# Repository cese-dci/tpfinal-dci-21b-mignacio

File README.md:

## Trabajo práctico final de la asignatura DCI ##
Este repositorio contiene el trabajo práctico final para la asignatura de Diseño de Circuitos Impresos de la carrera de posgrado de FIUBA.

* Autor: Ignacio Moya
* Título corto del trabajo:  Poncho MAX9924 para EDU-CIAA 
* Descripción:  Poncho para el circuito integrado MAX9924, que funciona como interface para sensores de reluctancia variable.

## Licencia de este trabajo ##
GPL http://www.gnu.org/licenses/gpl-3.0.html

## Estructura del repositorio ##

* doc: Toda la información sobre el circuito, principalmente de autoría o procesamiento propio. Por ejemplo:
  * Notas de ingeniería propias.
  * Notas de aplicación propias.
  * Estudios previos, estado del arte, resumen de las investigaciones.
  * Notas con cálculos.
  * Dibujos adicionales.
  * Fotos de los prototipos.
  * Presupuestos, cotizaciones.
* info: Toda la iformación recolectada, principalmente de terceros, como por ejemplo:
  * Hojas de datos.
  * Notas de aplicación.
  * Info de productos comerciales.
  * Info en internet.
* pcb: Archivos de diseño esquemático y pcb.

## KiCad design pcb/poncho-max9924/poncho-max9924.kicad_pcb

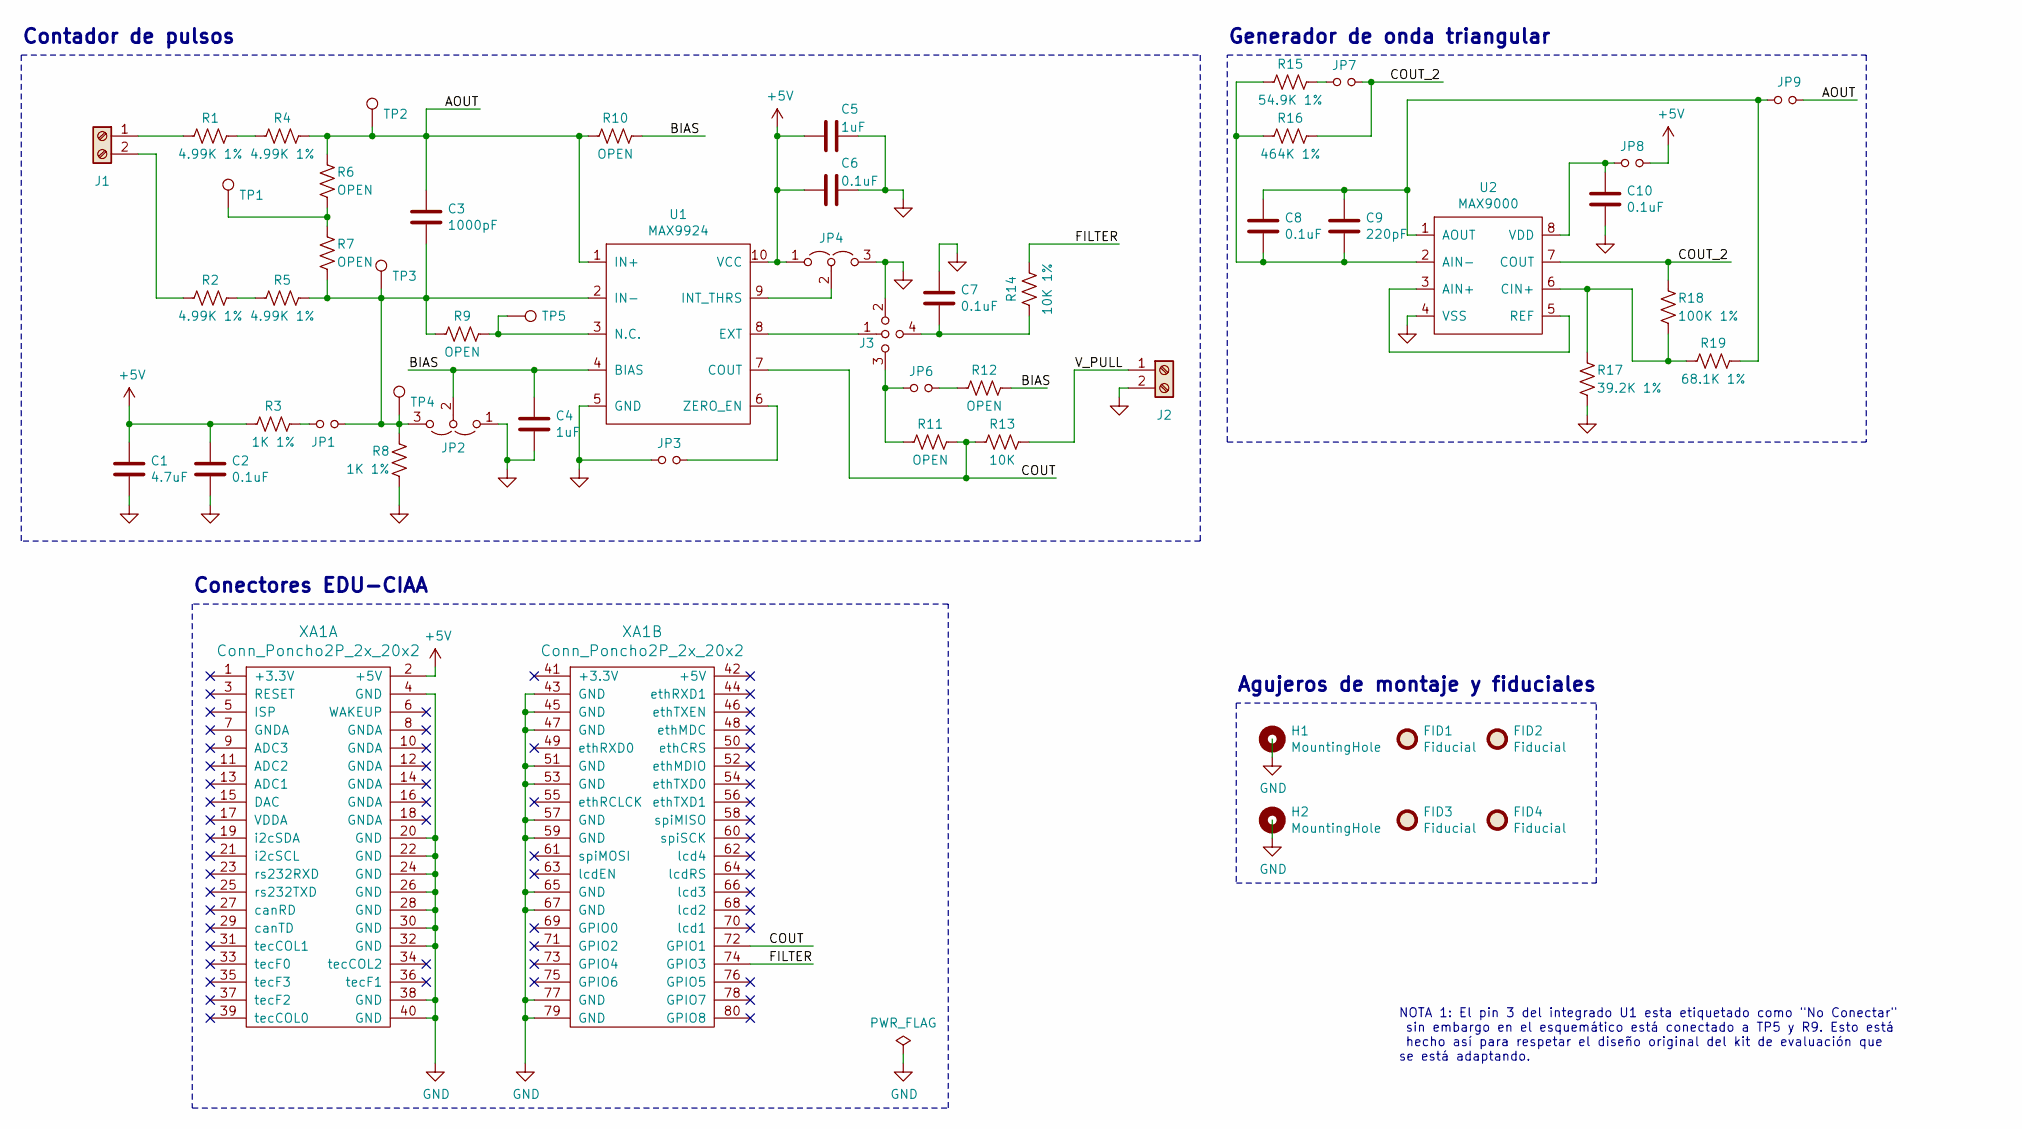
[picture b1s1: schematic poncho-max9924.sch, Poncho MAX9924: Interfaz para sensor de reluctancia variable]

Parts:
C1: 4.7uF; C_0805_2012Metric_Pad1.18x1.45mm_HandSolder
C2, C6, C7, C8, C10: 0.1uF; C_0805_2012Metric_Pad1.18x1.45mm_HandSolder
C3: 1000pF; C_0805_2012Metric_Pad1.18x1.45mm_HandSolder
C4, C5: 1uF; C_0805_2012Metric_Pad1.18x1.45mm_HandSolder
C9: 220pF; C_0805_2012Metric_Pad1.18x1.45mm_HandSolder
FID1, FID2, FID3, FID4: Fiducial; Fiducial_0.5mm_Mask1mm
H1, H2: MountingHole; MountingHole_3.5mm_Pad
J1, J2: Screw_Terminal_01x02; TerminalBlock_bornier-2_P5.08mm
J3: jumper_4_open; PinHeader_1x03_1x01_P2.54mm_Vertical
JP1, JP3, JP6, JP7, JP8, JP9: Jumper_NO_Small; PinHeader_1x02_P2.54mm_Vertical
JP2, JP4: Jumper_3_Open; PinHeader_1x03_P2.54mm_Vertical
R1, R2, R4, R5: 4.99K 1%; R_0805_2012Metric_Pad1.20x1.40mm_HandSolder
R3, R8: 1K 1%; R_0805_2012Metric_Pad1.20x1.40mm_HandSolder
R6, R7, R9, R10, R11, R12: OPEN; R_0805_2012Metric_Pad1.20x1.40mm_HandSolder
R13: 10K; R_0805_2012Metric_Pad1.20x1.40mm_HandSolder
R14: 10K 1%; R_0805_2012Metric_Pad1.20x1.40mm_HandSolder
R15: 54.9K 1%; R_0805_2012Metric_Pad1.20x1.40mm_HandSolder
R16: 464K 1%; R_0805_2012Metric_Pad1.20x1.40mm_HandSolder
R17: 39.2K 1%; R_0805_2012Metric_Pad1.20x1.40mm_HandSolder
R18: 100K 1%; R_0805_2012Metric_Pad1.20x1.40mm_HandSolder
R19: 68.1K 1%; R_0805_2012Metric_Pad1.20x1.40mm_HandSolder
TP1, TP2, TP3, TP4, TP5: TestPoint; TestPoint_Pad_D2.0mm
U1: MAX9924; SOP50P490X110-10N; Digikey PN MAX9924UAUB+T
U2: MAX9000; SOP65P490X110-8N; Digikey PN MAX9000ESA+
XA1: Conn_Poncho2P_2x_20x2; Conn_Poncho_SinBorde

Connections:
+5V: C1.1, C2.1, C5.2, C6.2, JP4.1 (A), JP8.2, R3.2, U1.10 (VCC), XA1.2 (+5V)
/AOUT: C3.1, JP9.2, R4.1, R6.1, R10.2, TP2.1, U1.1 (IN+)
/BIAS: C4.1, JP2.2 (C), R10.1, R12.1, U1.4 (BIAS)
/COUT: R11.1, R13.2, U1.7 (COUT), XA1.72 (GPIO1)
/COUT_2: JP7.1, R16.1, R18.1, U2.7 (COUT)
/FILTER: R14.1, XA1.74 (GPIO3)
/V_PULL: J2.1, R13.1
GND: C1.2, C2.2, C4.2, C5.1, C6.1, C7.1, C10.1, J2.2, J3.2, JP2.1 (A), JP3.2, JP4.3 (B), R8.1, R17.2, U1.5 (GND), U2.4 (VSS), XA1.4 (GND), XA1.20 (GND), XA1.22 (GND), XA1.24 (GND), XA1.26 (GND), XA1.28 (GND), XA1.30 (GND), XA1.32 (GND), XA1.38 (GND), XA1.40 (GND), XA1.43 (GND), XA1.45 (GND), XA1.47 (GND), XA1.51 (GND), XA1.53 (GND), XA1.57 (GND), XA1.59 (GND), XA1.65 (GND), XA1.67 (GND), XA1.77 (GND), XA1.79 (GND)
unnamed: C3.2, JP1.1, JP2.3 (B), R5.1, R7.2, R8.2, R9.2, TP3.1, TP4.1, U1.2 (IN-)
unnamed: C7.2, J3.4, R14.2
unnamed: C8.1, C9.1, R15.2, R16.2, U2.2 (AIN-)
unnamed: C8.2, C9.2, JP9.1, R19.1, U2.1 (AOUT)
unnamed: C10.2, JP8.1, U2.8 (VDD)
unnamed: J1.1, R1.2
unnamed: J1.2, R2.2
unnamed: J3.1, U1.8 (EXT)
unnamed: J3.3, JP6.2, R11.2
unnamed: JP1.2, R3.1
unnamed: JP3.1, U1.6 (ZERO_EN)
unnamed: JP4.2 (C), U1.9 (INT_THRS)
unnamed: JP6.1, R12.2
unnamed: JP7.2, R15.1
unnamed: R1.1, R4.2
unnamed: R2.1, R5.2
unnamed: R6.2, R7.1, TP1.1
unnamed: R9.1, TP5.1, U1.3 (N.C.)
unnamed: R17.1, R18.2, R19.2, U2.6 (CIN+)
unnamed: U2.3 (AIN+), U2.5 (REF)

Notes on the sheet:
Generador de onda triangular
Contador de pulsos
Conectores EDU-CIAA
NOTA 1: El pin 3 del integrado U1 esta etiquetado como "No Conectar" sin embargo en el esquemático está conectado a TP5 y R9. Esto está hecho así para respetar el diseño original del kit de evaluación que se está adaptando.
Agujeros de montaje y fiduciales

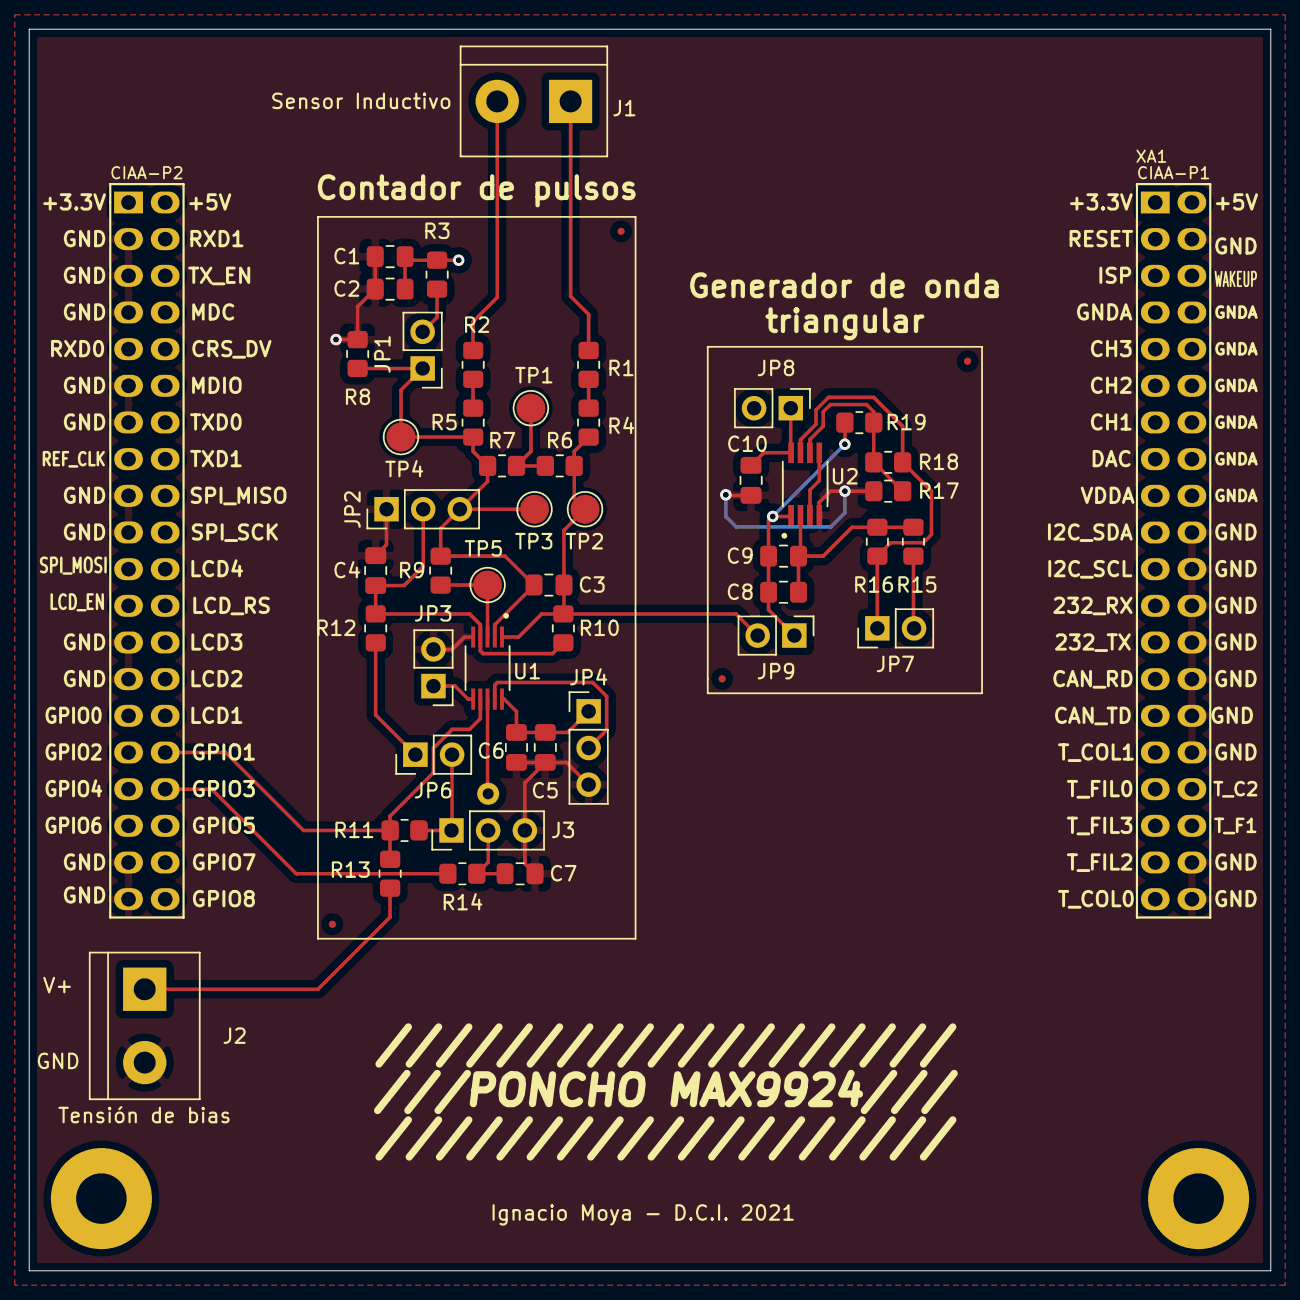
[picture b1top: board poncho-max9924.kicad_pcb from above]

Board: 2 copper layers, 86.0 x 86.0 mm, 54 parts (0 on the bottom side), 28 nets.

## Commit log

2021-07-04 Se completaron datos de autor y licencia en README.md raíz y se agregaron hojas de datos del circuito integrado y del módulo de evaluación
2021-07-04 Se agregó información de la propuesta
2021-07-04 Se crea proyecto de kikad y se agrega bibliotecas de poncho ciaa
2021-07-11 esquematico copiado 100%, falta adaptar a poncho
2021-07-17 avances en el esquematico
2021-07-20 Esquematico listo para primer revision
2021-07-21 Se realizaron correcciones en base a comentarios del revisor M. Castello
2021-07-22 Correccion de error ERC en terminal de masa
2021-07-24 Se crearon huellas faltantes. Se asignaron huellas a todos los componentes y se hizo una primera ubicacion de componentes en el circuito impreso
2021-07-27 Se agregaron modelos 3D de todos los componentes y sus footprints. Se re trabajo el posicionamiento de componentes en la placa.
2021-08-10 primer routeado
2021-08-14 correcciones y ruteo listo, falta hacer U2 multiparte
2021-08-16 Se corrigieron errores en DRC y se agregó más info de fabricación en PCB

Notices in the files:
pcb/poncho-max9924/poncho-max9924.kicad_pcb:
Licencia: GPL
